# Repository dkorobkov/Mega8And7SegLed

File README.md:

# Mega8And7SegLed
Universal PCB (55*65 mm) with Atmega8 (TQFP32), VUSB and 2-4 digit 7-segment LED (or chinese "Nokia 5110" LCD) for generic projects. EAGLE files and Gerber, Atmel Studio 6.2 example project (C).

See https://github.com/dkorobkov/Mega8And7SegLed/blob/master/board_top.JPG for board look and 
https://github.com/dkorobkov/Mega8And7SegLed/blob/master/LEDBoard.mp4 for its operation.

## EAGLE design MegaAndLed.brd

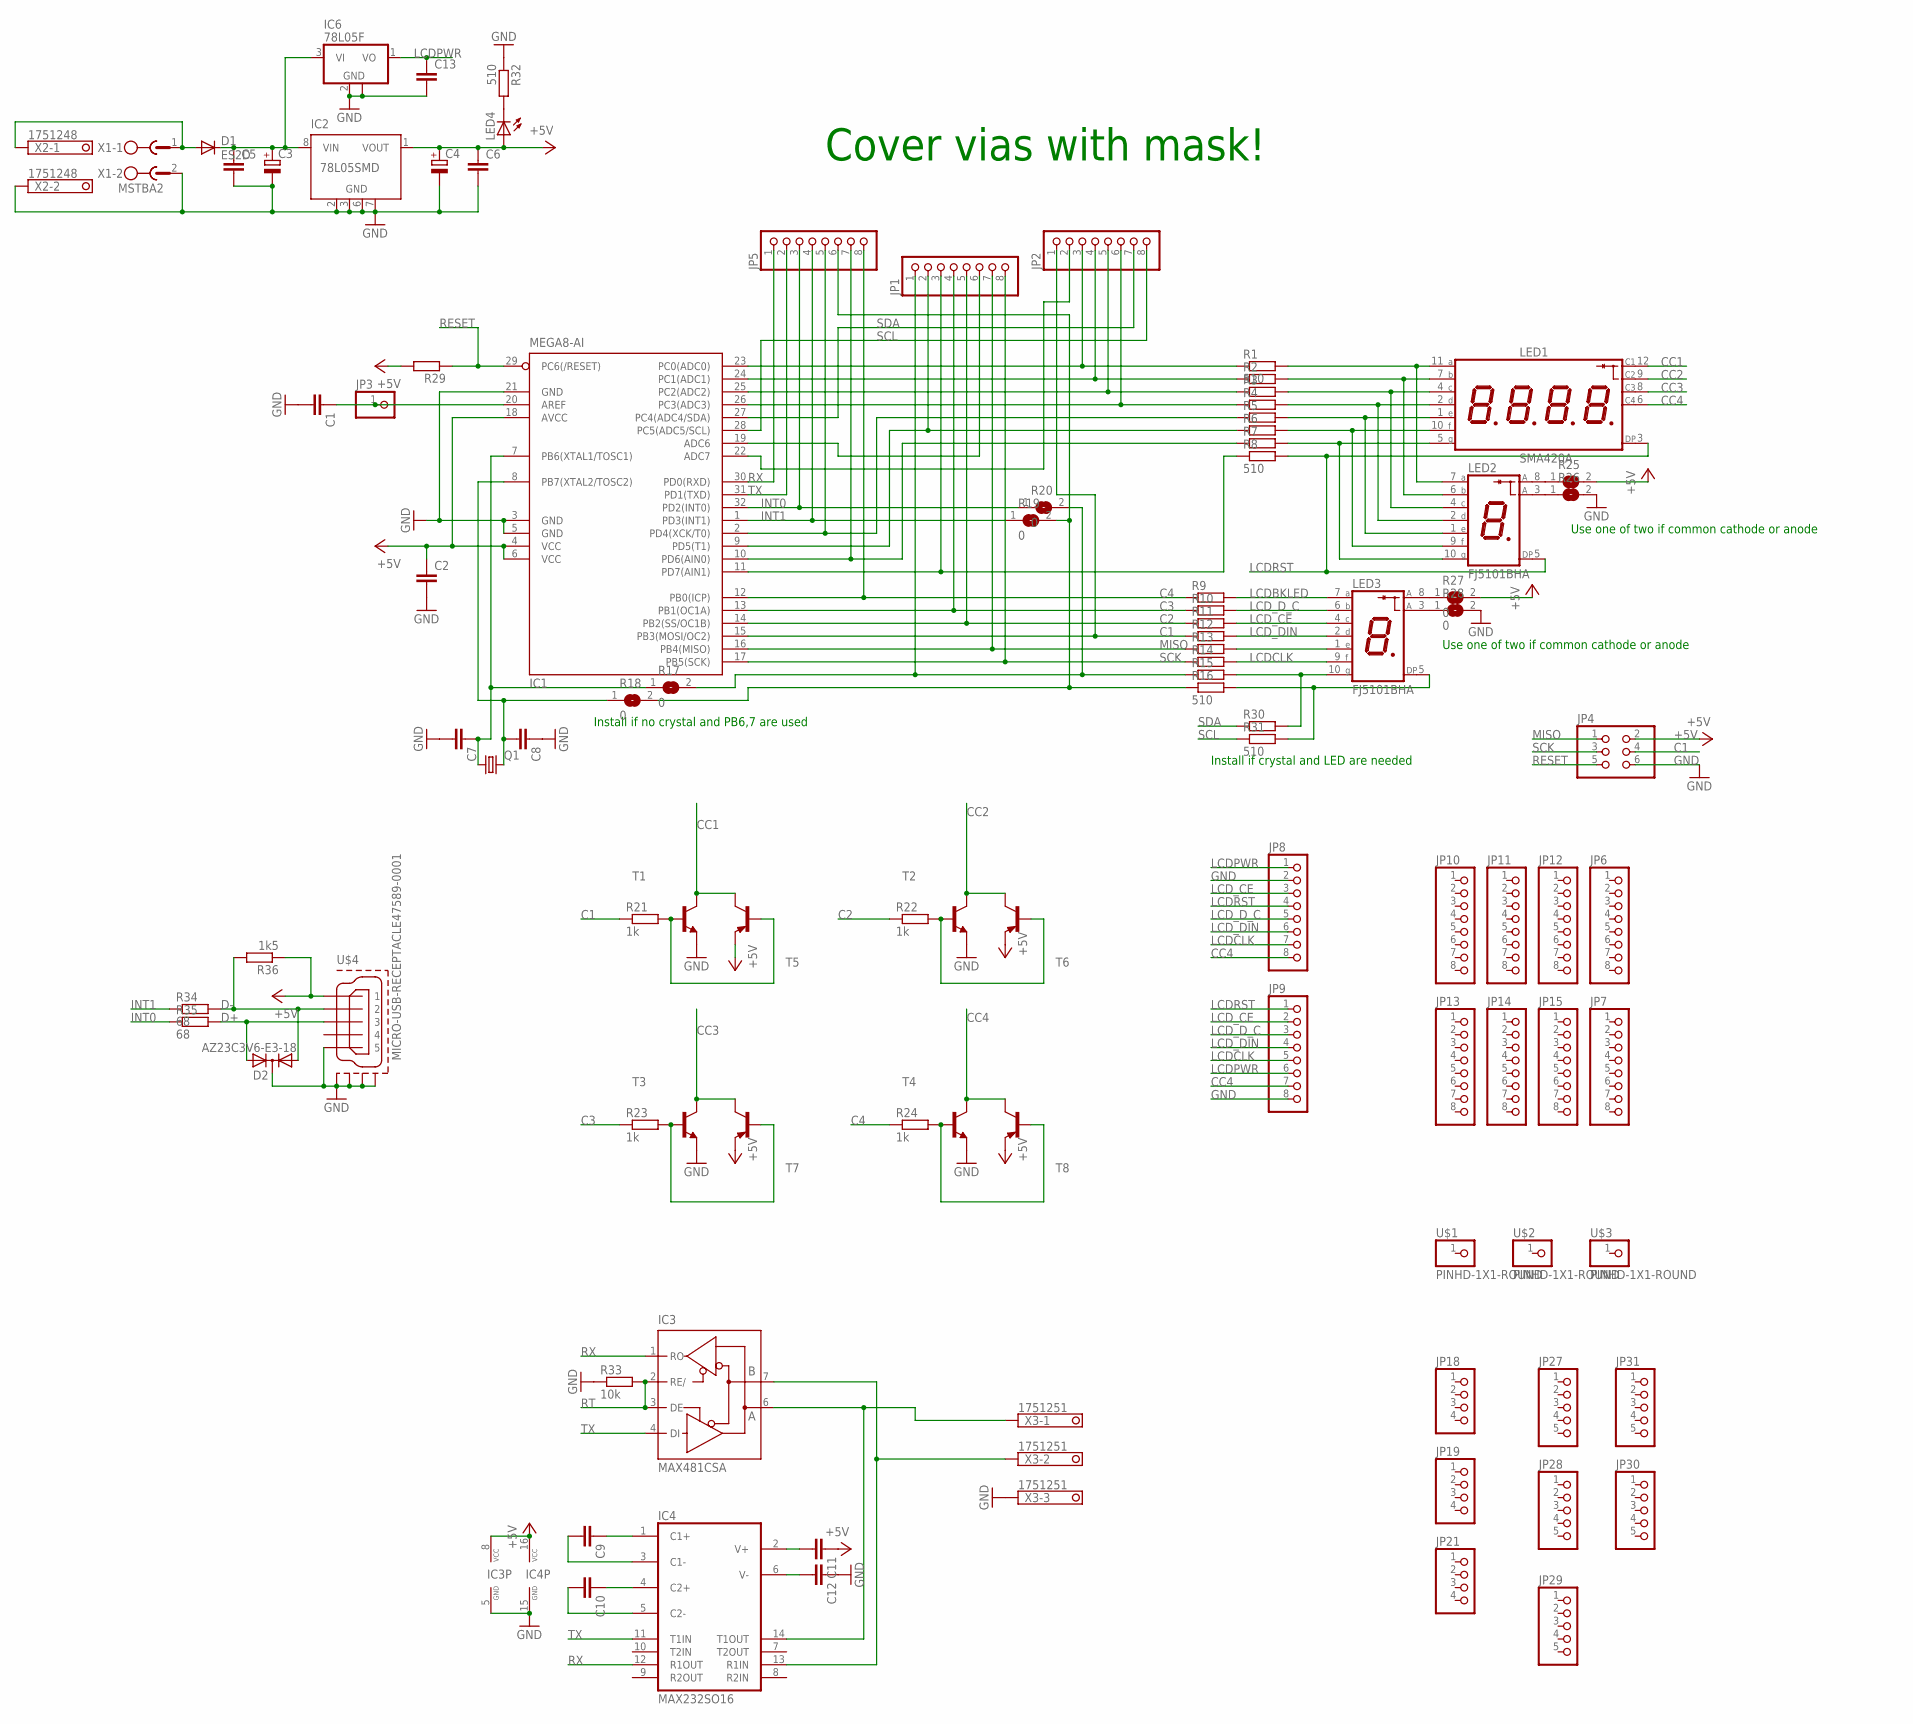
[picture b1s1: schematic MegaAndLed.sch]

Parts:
C1, C2, C5, C6, C7, C8, C9, C10, C11, C12, C13: C-EUC0805; C0805
C3, C4: CPOL-EUSMCC; SMC_C
D1: ES2D; SMB
D2: AZ23C3V6-E3-18; SOT23
IC1: MEGA8-AI; TQFP32-08
IC2: 78L05SMD; SO08
IC3: MAX481CSA; SO08
IC4: MAX232SO16; SO16
IC6: 78L05F; SOT89
JP1, JP2, JP5, JP6, JP7, JP8, JP9, JP10, JP11, JP12, JP13, JP14, JP15: PINHD-1X8-ROUND; 1X08-ROUND
JP3: PINHD-1X1; 1X01
JP4: PINHD-2X3; 2X03
JP18, JP19, JP21: PINHD-1X4-ROUND; 1X04-ROUND
JP27, JP28, JP29, JP30, JP31: PINHD-1X5-ROUND; 1X05-ROUND
LED1: SMA420A; 7X4-LED
LED2, LED3: FJ5101BHA; LA-401
LED4: LEDCHIPLED_1206; CHIPLED_1206
Q1: CRYSTALHC49U-H; HC49U-H
R1, R8, R16, R31, R32: 510; R0805
R2, R3, R4, R5, R6, R7, R9, R10, R11, R12, R13, R14, R15, R29, R30: R-EU_R0805; R0805
R17, R18, R19, R20, R27, R28: 0; SJ
R21, R22, R23, R24: 1k; R0805
R25, R26: SJ
R33: 10k; R0805
R34, R35: 68; R0805
R36: 1k5; R0805
T1, T2, T3, T4: BCW31-NPN-SOT23-BEC; SOT23-BEC
T5, T6, T7, T8: MMBTA56-SOT23; SOT23
U$1, U$2, U$3: PINHD-1X1-ROUND; 1X01-ROUND
U$4: MICRO-USB-RECEPTACLE47589-0001; 47589-0001
X1: MSTBA2
X2: 1751248
X3: 1751251

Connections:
+5V: C2.1, C4.+, C6.1, C11.1, IC1.4 (VCC), IC1.6 (VCC), IC1.18 (AVCC), IC2.1 (VOUT), IC3.8 (VCC), IC4.16 (VCC), JP4.2, LED4.A, R25.2, R27.2, R29.2, R36.1, T5.2 (E), T6.2 (E), T7.2 (E), T8.2 (E), U$4.1
C1: IC1.15 (PB3(MOSI/OC2)), JP2.1, JP4.4, R12.1, R21.1
C2: IC1.14 (PB2(SS/OC1B)), JP1.5, R11.1, R22.1
C3: IC1.13 (PB1(OC1A)), JP1.4, R10.1, R23.1
C4: IC1.12 (PB0(ICP)), JP5.8, R9.1, R24.1
CC1: LED1.12 (C), T1.C, T5.3 (C)
CC2: LED1.9 (C), T2.C, T6.3 (C)
CC3: LED1.8 (C), T3.C, T7.3 (C)
CC4: JP8.8, JP9.7, LED1.6 (C), T4.C, T8.3 (C)
D+: D2.2 (A2), R35.2, U$4.3
D-: D2.1 (A1), R34.2, R36.2, U$4.2
GND: C1.2, C2.2, C3.-, C4.-, C5.2, C6.2, C7.2, C8.1, C12.1, C13.2, D2.3 (C), IC1.3 (GND), IC1.5 (GND), IC1.21 (GND), IC2.2 (GND), IC2.3 (GND), IC2.6 (GND), IC2.7 (GND), IC3.5 (GND), IC4.15 (GND), IC6.2 (GND), IC6.2@1 (GND), JP4.6, JP8.2, JP9.8, R26.2, R28.2, R32.1, R33.1, T1.E, T2.E, T3.E, T4.E, U$4.5, U$4.CASING1 (GND1), U$4.CASING2 (GND2), U$4.CASING3 (GND3), U$4.CASING4 (GND4), X1.2, X2.2, X3.3
INT0: IC1.32 (PD2(INT0)), JP5.3, R20.1, R35.1
INT1: IC1.1 (PD3(INT1)), JP5.4, R19.1, R34.1
LCDBKLED: LED3.7 (A), R9.2
LCDCLK: JP8.7, JP9.5, LED3.9 (F), R14.2
LCDPWR: C13.1, IC6.1 (VO), JP8.1, JP9.6
LCDRST: JP8.4, JP9.1, LED1.3 (DP), LED2.5 (DP), R8.2
LCD_CE: JP8.3, JP9.2, LED3.4 (C), R11.2
LCD_DIN: JP8.6, JP9.4, LED3.2 (D), R12.2
LCD_D_C: JP8.5, JP9.3, LED3.6 (B), R10.2
MISO: IC1.16 (PB4(MISO)), JP1.7, JP4.1, R13.1
unnamed: C3.+, C5.1, D1.C, IC2.8 (VIN), IC6.3 (VI)
unnamed: IC1.23 (PC0(ADC0)), JP2.3, R1.1
unnamed: IC1.24 (PC1(ADC1)), JP2.4, R2.1
unnamed: IC1.25 (PC2(ADC2)), JP2.5, R3.1
unnamed: R21.2, T1.B, T5.1 (B)
unnamed: R22.2, T2.B, T6.1 (B)
unnamed: IC1.26 (PC3(ADC3)), JP2.6, R4.1
unnamed: C1.1, IC1.20 (AREF), JP3.1
unnamed: LED2.8 (C), R25.1
unnamed: LED2.3 (C), R26.1
unnamed: LED3.8 (C), R27.1
unnamed: LED3.3 (C), R28.1
unnamed: IC1.19 (ADC6), JP1.6
unnamed: IC1.2 (PD4(XCK/T0)), JP5.5, R5.1
unnamed: R23.2, T3.B, T7.1 (B)
unnamed: R24.2, T4.B, T8.1 (B)
unnamed: IC1.22 (ADC7), JP2.2
unnamed: IC1.9 (PD5(T1)), JP1.2, R6.1
unnamed: IC1.10 (PD6(AIN0)), JP5.7, R7.1
unnamed: LED4.C, R32.2
unnamed: C9.1, IC4.1 (C1+)
unnamed: D1.A, X1.1, X2.1
unnamed: C10.1, IC4.4 (C2+)
unnamed: IC1.11 (PD7(AIN1)), JP1.3, R8.1
unnamed: C8.2, IC1.8 (PB7(XTAL2/TOSC2)), Q1.2, R18.1
unnamed: C10.2, IC4.5 (C2-)
unnamed: C9.2, IC4.3 (C1-)
unnamed: C11.2, IC4.2 (V+)
unnamed: JP5.6, R16.1, R18.2, R19.2
unnamed: LED1.11 (A), LED2.7 (A), R1.2
unnamed: LED1.7 (B), LED2.6 (B), R2.2
unnamed: LED1.4 (C), LED2.4 (C), R3.2
unnamed: LED1.2 (D), LED2.2 (D), R4.2
unnamed: LED1.1 (E), LED2.1 (E), R5.2
unnamed: LED1.10 (F), LED2.9 (F), R6.2
unnamed: LED1.5 (G), LED2.10 (G), R7.2
unnamed: LED3.1 (E), R13.2
unnamed: LED3.10 (G), R15.2, R30.2
unnamed: LED3.5 (DP), R16.2, R31.2
unnamed: C12.2, IC4.6 (V-)
unnamed: JP1.1, R15.1, R17.2, R20.2
unnamed: IC3.6 (A), IC4.14 (T1OUT), X3.1
unnamed: IC3.7 (B), IC4.13 (R1IN), X3.2
unnamed: C7.1, IC1.7 (PB6(XTAL1/TOSC1)), Q1.1, R17.1
RESET: IC1.29 (PC6(/RESET)), JP4.5, R29.1
RT: IC3.2 (RE/), IC3.3 (DE), R33.2
RX: IC1.30 (PD0(RXD)), IC3.1 (RO), IC4.12 (R1OUT), JP5.1
SCK: IC1.17 (PB5(SCK)), JP1.8, JP4.3, R14.1
SCL: IC1.28 (PC5(ADC5/SCL)), JP2.8, R31.1
SDA: IC1.27 (PC4(ADC4/SDA)), JP2.7, R30.1
TX: IC1.31 (PD1(TXD)), IC3.4 (DI), IC4.11 (T1IN), JP5.2

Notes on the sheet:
Install if crystal and LED are needed
Use one of two if common cathode or anode
Install if no crystal and PB6,7 are used
Cover vias with mask!

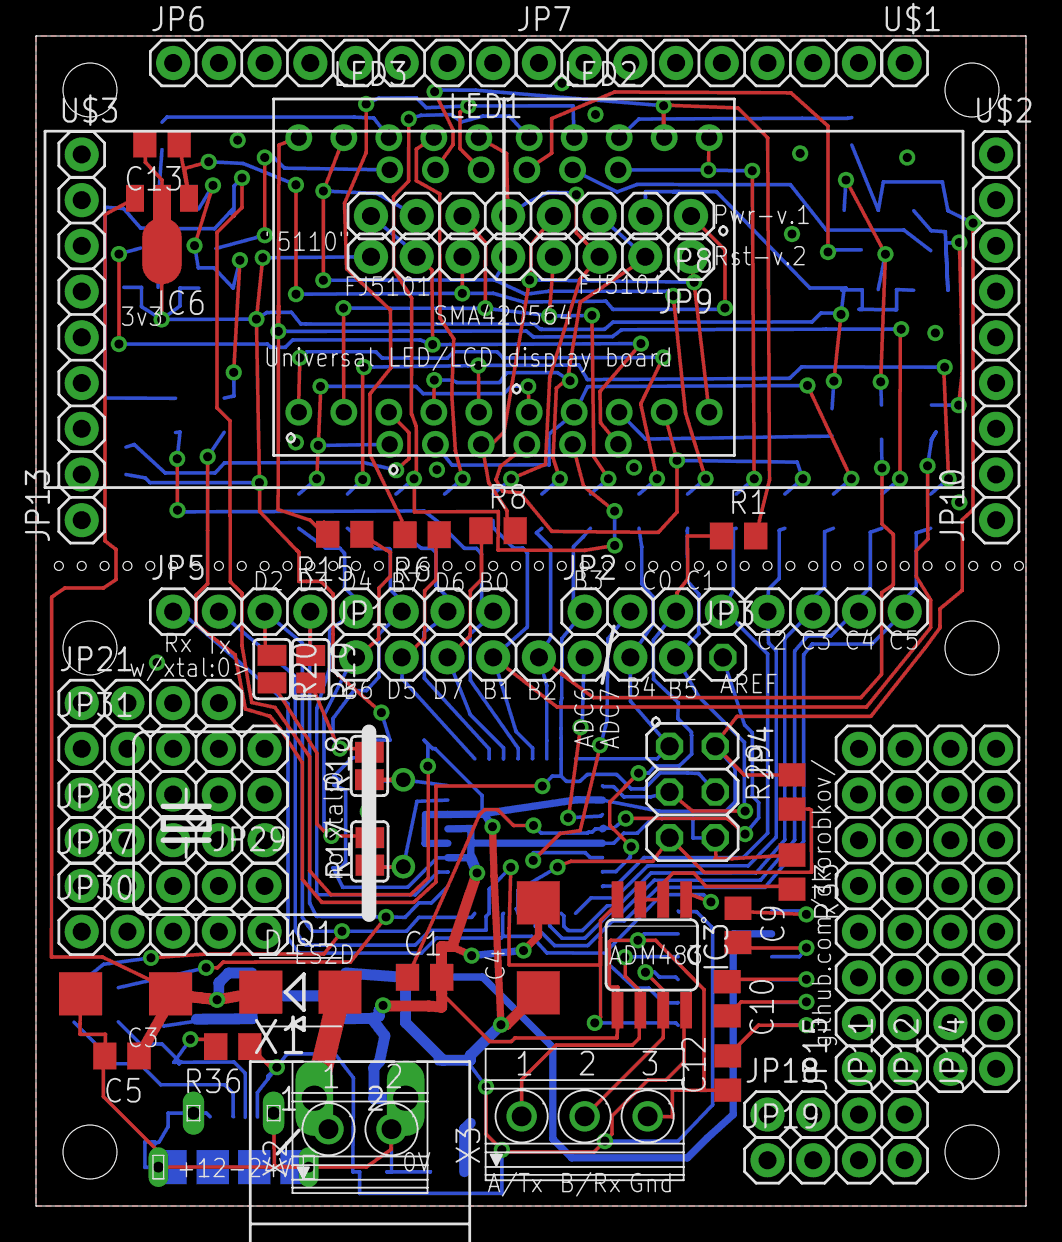
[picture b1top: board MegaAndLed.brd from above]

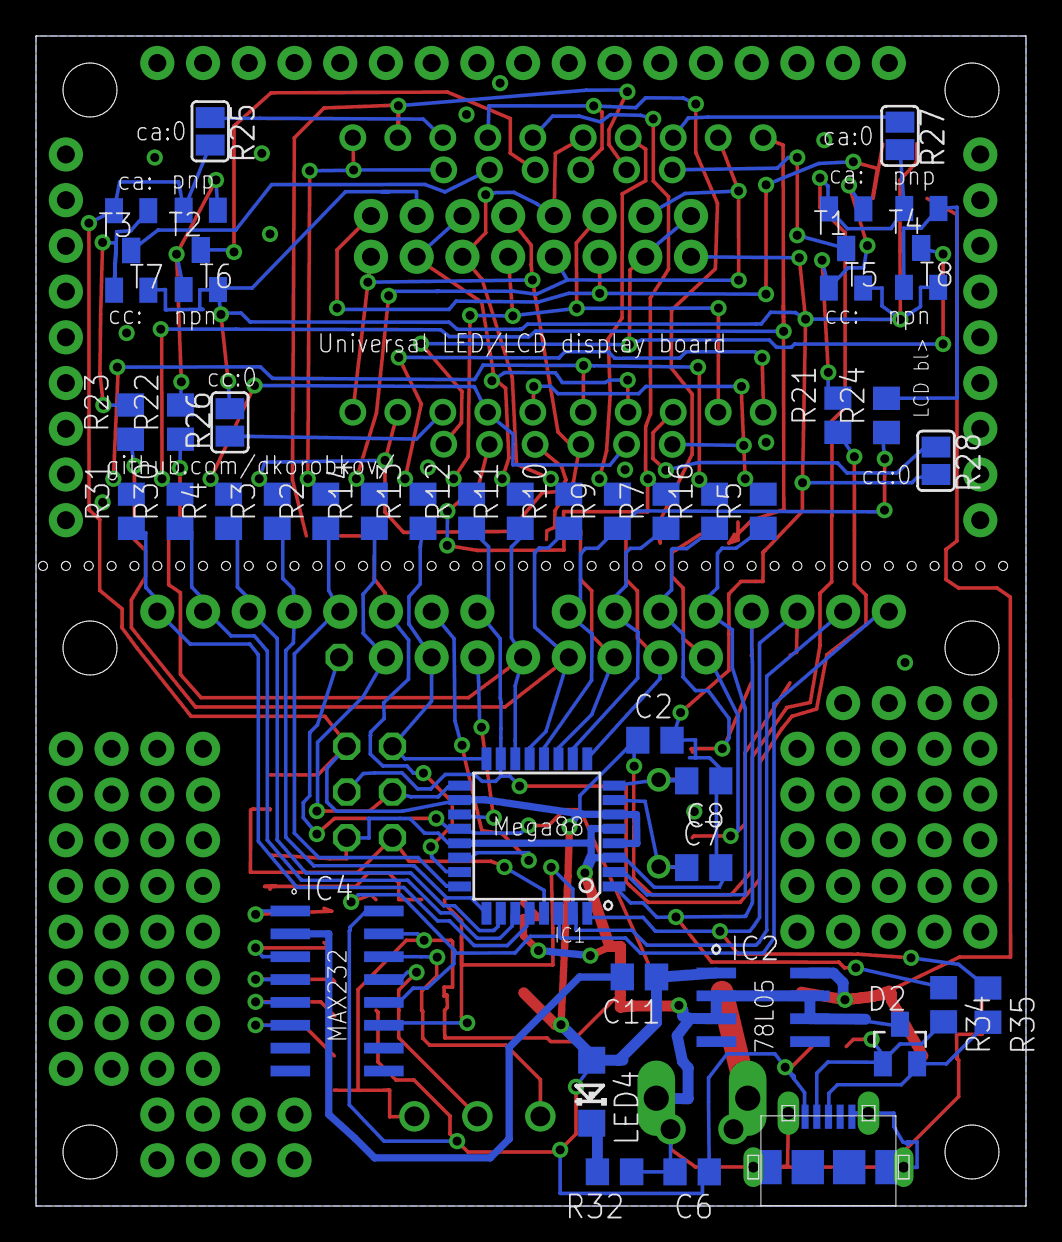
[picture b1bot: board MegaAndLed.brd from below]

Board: 2 copper layers, 55.0 x 65.0 mm, 99 parts (44 on the bottom side), 73 nets.

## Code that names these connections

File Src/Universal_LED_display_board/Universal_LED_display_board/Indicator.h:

/*
 * Indicator.h
 *
 * Created: 12.12.2016 17:53:17
 *  Author: https://github.com/dkorobkov
 
 Code is for ATMega8 and pin compatible devices.
 
 For SMA420564 (4*7-seg, common cathode):
 You need to drive one cathode and 0 to 8 anodes to turn on a single digit.
 Current flows from ATMega pin through LED to another pin(s).
 +-----+-------+-----------+------------+
 | LED | Descr |  MCU pin  | Level for  |
 | pin |       | (ATMega8) | lighting   |
 +-----+-------+-----------+------------+
 | 1   |  e    |  PD4   2  |     1      |
 | 2   |  d    |  PC3   26 |     1      |
 | 3   |  .    |  PD7   11 |     1      |
 | 4   |  c    |  PC2   25 |     1      |
 | 5   |  g    |  PD6   10 |     1      |
 | 6   |  C4   |  PB0   12 |     1      |
 | 7   |  b    |  PC1   24 |     1      |
 | 8   |  C3   |  PB1   13 |     1      |
 | 9   |  C2   |  PB2   14 |     1      |
 | 10  |  f    |  PD5   9  |     1      |
 | 11  |  a    |  PC0   23 |     1      |
 | 12  |  C1   |  PB3   15 |     1      |
 +-----+-------+-----------+------------+
 
 For 2*FJ5101BH (7-seg, common anode):
 All segments are driven simultaneously (16 MCU outputs are used)
 
 +-----+-------+-----------+------------+
 | LED1| Descr |  MCU pin  | Level for  |
 | pin |       | (ATMega8) | lighting   |
 +-----+-------+-----------+------------+
 | 1   |  e    |  PD4   2  |     0      |
 | 2   |  d    |  PC3   26 |     0      |
 | 3   | Anode |  +5V      |     1      |
 | 4   |  c    |  PC2   25 |     0      |
 | 5   |  dp   |  PD7   11 |     0      |
 | 6   |  b    |  PC1   24 |     0      |
 | 7   |  a    |  PC0   23 |     0      |
 | 8   | Anode |  +5V      |     1      |
 | 9   |  f    |  PD5   9  |     0      |
 | 10  |  g    |  PD6   10 |     0      |
 +-----+-------+-----------+------------+
 +-----+-------+-----------+------------+
 | LED2| Descr |  MCU pin  | Level for  |
 | pin |       | (ATMega8) | lighting   |
 +-----+-------+-----------+------------+
 | 1   |  e    |  PB4   16 |     0      |
 | 2   |  d    |  PB3   15 |     0      |
 | 3   | Anode |  +5V      |     1      |
 | 4   |  c    |  PB2   14 |     0      |
 | 5   |  dp   |  PB7   8  |     0      | USES_CRYSTAL=0
 | 5   |  dp   |  PC5   28 |     0      | USES_CRYSTAL=1
 | 6   |  b    |  PB1   13 |     0      |
 | 7   |  a    |  PB0   12 |     0      |
 | 8   | Anode |  +5V      |     1      |
 | 9   |  f    |  PB5   17 |     0      |
 | 10  |  g    |  PB6   7  |     0      | USES_CRYSTAL=0
 | 10  |  g    |  PC4   27 |     0      | USES_CRYSTAL=1
 +-----+-------+-----------+------------+
 
 This code was tested with:
  NUM_DIGITS=4 and COMMON_PIN=COMMON_CATHODE
  NUM_DIGITS=2 and COMMON_PIN=COMMON_ANODE and USES_CRYSTAL=0
 
 */ 


#ifndef INDICATOR_H_
#define INDICATOR_H_
#define COMMON_CATHODE 0
#define COMMON_ANODE 1

// User settable defines.

// Set type of your indicator.
#define COMMON_PIN COMMON_ANODE

// Set number of digits on your indicator. Can be 2 or 4
// 4 is for SMA420564 and similar.
// 2 is for 2*FJ5101BH and similar.
#define NUM_DIGITS 2

// If 1-digit LEDs are installed there are two options. 
// If you need crystal (i.e. Atmel's internal calibrated RC oscillator
// is not sufficient) you will short R30 and R31 "w/xtal". If you need SDA and SCL
// you will have to work __without__ crystal and short R17, R18 "no xtal".
#if NUM_DIGITS == 2
	#define USES_CRYSTAL 0 // LED connected to PB6, PB7
//	#define USES_CRYSTAL 1 // LED connected to PC4, PC5
#endif

// Set maximum string length for display. Affects free RAM.
// (Of course, for some applications you will want to use PROGMEM
// for string storage and display, rewriting the code is up to you)
#define MAX_STRING_LEN 32

// When displaying moving string the constants below are used.
#define MOVING_START_TIME 1500 // Show beginning of string during this milliseconds
#define MOVING_MID_TIME 500    // Milliseconds between 1-char moves
#define MOVING_END_TIME	1500   // Show end of string during this milliseconds

// *************** No user settable variables below this line *****************

// For dynamic display, call me as often as possible
// (but about once in millisecond).
// Tell me number of milliseconds passed from previous update
// so I could move the string being displayed.
void Update(unsigned char ms);

// Fills indicator from PROGMEM
void StringToIndicator_P(const char /*PROGMEM*/ * pStr);

// Fills indicator from RAM
void StringToIndicator(const char * pStr);

// Sets up MCU I/O. Call before usage.
void InitIndicator();




#endif /* INDICATOR_H_ */

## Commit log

2016-11-21 Board received from pcbway.com !
2016-12-12 Source code for ATMega8 to work (yet) with 4-digit LED indicator.
2017-01-17 Example of stopwatch with millisecond precision (used for machine vision camera benchmarking)
2017-01-17 Soldering components for 4-pos 7-seg LED
2017-01-28 Fixed unrouted wire from crystal to R18, C8
2017-01-29 2*7-seg FJ5101BH is now supported.
2017-01-29 Components to be soldered if using FJ5101BH
2019-01-29 Added settings for common anode LEDs
2019-08-26 Update to work with common anode LED indicators (settable in Indicator.h)
2019-08-27 Migrate to Atmel Studio 7 Add MCU above Mega8 (changes in register names)
2020-02-26 Fixed many issues found so far. Added chinese "Nokia 5110" LCD connection (two pinouts met in the market) Added microUSB for powering up and V-USB (https://www.obdev.at/products/vusb/index.html)
2020-02-26 Update README.md
    New features
2022-03-22 Fixing repo
2022-03-22 Two pulse generator with UART for ATMega8L
